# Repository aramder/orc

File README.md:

<div align="center">

<picture>
  <source media="(prefers-color-scheme: dark)" srcset="docs/media/banner-dark.svg">
  <source media="(prefers-color-scheme: light)" srcset="docs/media/banner-light.svg">
  
</picture>

**A replacement controller board for surplus Motorola PMUN1046A relay boxes — same relays and enclosure; open CAN control over plain terminal blocks instead of the proprietary wired link to the radio.**

Independent open-source project. Not affiliated with, endorsed by, or connected to Motorola Solutions, Inc. — see [TRADEMARKS.md](TRADEMARKS.md).

[**Project writeup and photos →**](https://aramd.net/PMUN1046A-Relay-Controller/)

**Safety:** this switches high-current DC in a vehicle. It is not safety qualified and must not be used for safety-critical functions. Read [DISCLAIMER.md](DISCLAIMER.md) before building anything.

</div>

---

## Why

The PMUN1046A **Universal Relay Controller (URC)** is a sealed 12 V automotive relay box — ten relay outputs at 15 A each, per-channel fusing, and a busbar power input rated for up to two cables at 60 A each (Motorola's install manual), in a trunnion-mounted weatherproof chassis. Power goes straight to the busbar through cable glands — no special harness needed on the input side. Surplus units are common and cheap. Everything about it is desirable *except* that it only takes commands from a Motorola APX radio over a proprietary GCAI/USB link.

ORC replaces the controller board outright and makes the box a general-purpose, openly-controlled ten-channel power distribution module. **ORC** stands for Open Relay Controller.

ORC does not implement, emulate, or interoperate with the GCAI link. The controller board is an independent design that replaces the donor unit's controller board entirely; control is plain CAN or USB.

<details>
<summary><b>About the donor unit</b> (PMUN1046A Universal Relay Controller)</summary>
<br>

Motorola's URC ships as part of the APX mobile radio ecosystem — a sealed relay box meant to switch scene lighting, sirens, and other accessory loads from the radio head. The relay board and chassis are generic 12 V automotive gear; only the controller board and its proprietary GCAI/USB command link to the radio are Motorola-specific. The relay board is entirely passive (relays, fuses, terminal blocks, busbar — no drivers or regulator of its own); a small internal harness carries switched 9 V coil drive between it and the controller board. Power input has no special harness at all — it lands straight on the busbar through the enclosure's cable glands. ORC keeps the relay board and chassis, and replaces the controller board and its proprietary radio link with plain CAN over terminal blocks — no proprietary connector anywhere in this design.

</details>

## What it is

<table>
<tr>
<td width="50%" valign="top">

**Inherited from the donor unit**
- Ten switched channels, 15 A each
- Per-channel fusing + busbar
- Board-to-board coil-drive harness (P/N `0975931M01`) — the internal cable between the relay board and the controller board, carrying switched 9 V coil drive; *not* a power-input harness
- Sealed, trunnion-mounted chassis

</td>
<td width="50%" valign="top">

**Rebuilt on the new controller board**
- ESP32-C3 controller (native USB for programming only; CAN-exclusive control, no wireless)
- 9 V relay coil supply
- Ten relay driver stages
- CAN terminal blocks (no proprietary connector)

</td>
</tr>
</table>

Category-wise this is a **PDM** (power distribution module) — the sPOD / Switch-Pros class of device — with an open CAN control interface instead of a proprietary wired link to the radio.

## The board

<em>ORC Rev A (green, right) and the OEM control PCB it replaces (blue, left).</em>

<em>ORC Rev A installed in the donor enclosure, alongside the OEM relay board that stays.</em>

**Full writeup, build story, and more photos:** [Open Relay Controller for the Motorola PMUN1046A](https://aramd.net/PMUN1046A-Relay-Controller/).

## Repo structure

One repo for design inputs, hardware, and firmware — no split-repo overhead for a project this size:

| Path | Contents | Status |
|---|---|---|
| `docs/` | Design inputs, specs, architecture decisions | Active |
| `hardware/` | KiCad project — schematic, PCB, BOM | Schematic captured, boards fabricated, populated, and bring-up verified on real hardware |
| `firmware/` | PlatformIO / Arduino firmware | `canopen_app` is real application firmware (CAN + USB relay control), verified on real hardware |
| `tools/` | Host-side CAN/USB bench test scripts | Used against real hardware |

## License

Different parts of the repo carry different licenses. Full texts are in [LICENSES/](LICENSES/); each directory also carries its own `LICENSE` file.

| Path | License |
|---|---|
| `hardware/` | [CERN-OHL-W-2.0](LICENSES/CERN-OHL-W-2.0.txt) |
| `firmware/`, `tools/` | [Apache-2.0](LICENSES/Apache-2.0.txt) |
| `docs/` | [CC-BY-4.0](LICENSES/CC-BY-4.0.txt) |

Hardware and software are licensed separately because they are separate works: under CERN-OHL's own definitions the ESP32-C3 is an Available Component, so a hardware license on the board does not reach the code running on it. See [NOTICE](NOTICE) for the summary and [TRADEMARKS.md](TRADEMARKS.md) for trademark and affiliation.

## Status

**Real-hardware bring-up complete.** Boards were sent to fab 2026-08-02, came back populated, and have been bench-tested since 2026-08-10: the PCA9555/I2C-isolator chain, the full 10-channel relay-driver mapping, and the CAN (RPDO1/TPDO1/TPDO2/Heartbeat) and USB control paths have all been exercised on real hardware. Five real firmware bugs were found and fixed along the way — BUG-001 through BUG-005, see [docs/features/LOG.md](docs/features/LOG.md) for the full history — the last of which (a liveness stall under an absent/unpowered PCA9555) was verified on real hardware 2026-09-04. One real mechanical fault (a harness connector shorting against the enclosure chassis) was also found and fixed on the bench — see [docs/circuit-draft.md](docs/circuit-draft.md) for the follow-up enclosure-clearance item.

No further active development is planned barring a new bug. A couple of feature requests (FR-003, FR-005) remain open in the backlog but aren't being actively pursued right now.

Working conventions for part selection, asset verification, and check gates: [docs/hardware-workflow.md](docs/hardware-workflow.md). Bench test tooling for talking to a real board over CAN/USB from a PC: [tools/](tools/).

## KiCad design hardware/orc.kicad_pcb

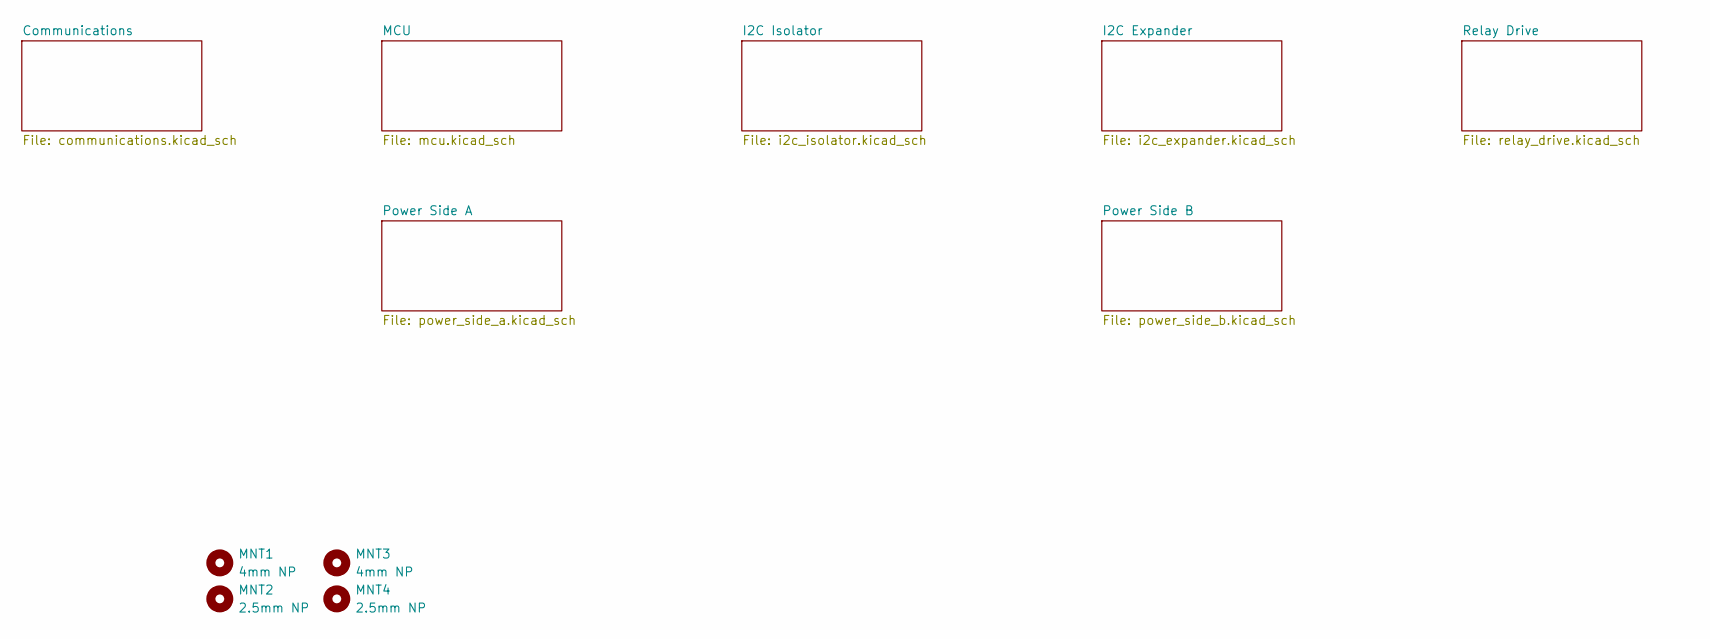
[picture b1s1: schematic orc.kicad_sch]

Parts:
MNT1, MNT3: 4mm NP; MountingHole_4mm
MNT2, MNT4: 2.5mm NP; MountingHole_2.5mm

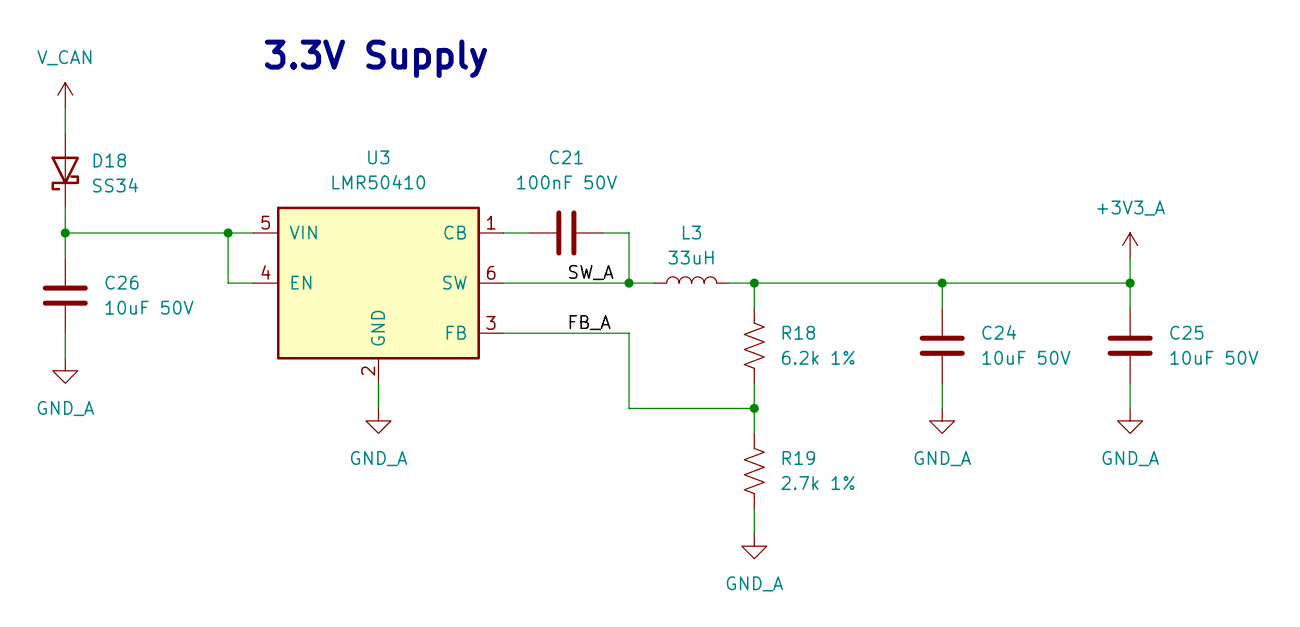
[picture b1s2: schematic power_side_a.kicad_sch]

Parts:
C21: 100nF 50V; C_0603_1608Metric; LCSC C14663
C24, C25, C26: 10uF 50V; C_0805_2012Metric; LCSC C440198
D18: SS34; D_SMA; LCSC C8678
L3: 33uH; L_Chilisin_BWVS00606045; Manufacturer Part Number SMDRI127-680MT; LCSC C285825
R18: 6.2k 1%; R_0603_1608Metric; LCSC C4260
R19: 2.7k 1%; R_0603_1608Metric; LCSC C13167
U3: LMR50410; SOT-23-6

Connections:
+3V3_A: C24.2, C25.2, L3.2, R18.2; also elsewhere on the board
/Power Side A/FB_A: R18.1, R19.2, U3.3 (FB)
/Power Side A/SW_A: C21.1, L3.1, U3.6 (SW)
GND_A: C24.1, C25.1, C26.1, R19.1, U3.2 (GND); also elsewhere on the board
unnamed: C26.2, D18.1 (K), U3.4 (EN), U3.5 (VIN)
unnamed: C21.2, U3.1 (CB)
V_CAN: D18.2 (A); also elsewhere on the board

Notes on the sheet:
3.3V Supply

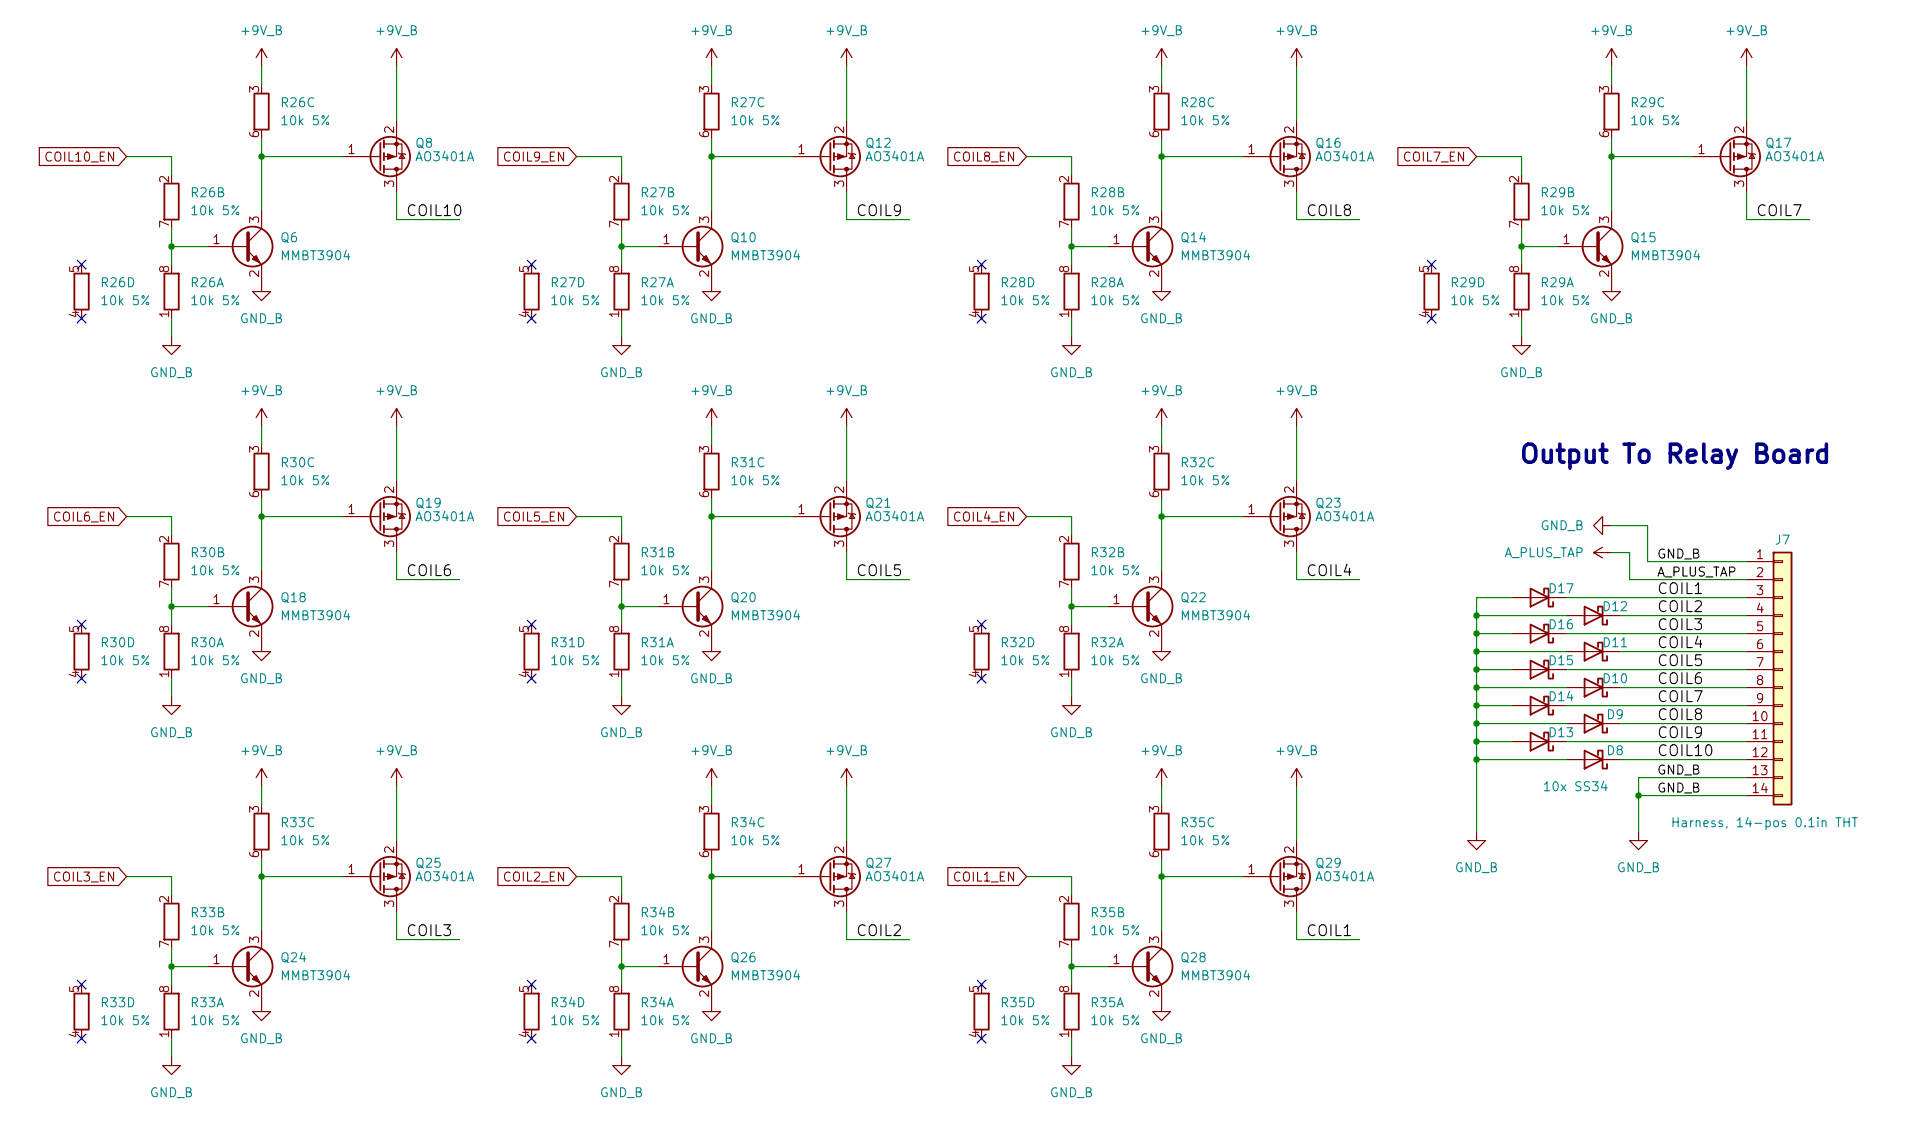
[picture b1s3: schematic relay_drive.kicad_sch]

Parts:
D8, D9, D10, D11, D12, D13, D14, D15, D16: SS34; D_SMA; LCSC C8678
D17: 10x SS34; D_SMA; LCSC C8678
J7: Harness, 14-pos 0.1in THT; PinSocket_1x14_P2.54mm_Vertical
Q6: MMBT3904; SOT-23; LCSC C20526
Q8, Q12, Q16, Q17, Q19, Q21, Q23, Q25, Q27, Q29: AO3401A; SOT-23; LCSC C15127
Q10, Q14, Q15, Q18, Q20, Q22, Q24, Q26, Q28: MMBT3904; SOT-23
R26, R27, R28, R29, R30, R31, R32, R33, R34, R35: 10k 5%; R_Array_Concave_4x0603; LCSC C29718

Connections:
+9V_B: Q8.2 (S), Q12.2 (S), Q16.2 (S), Q17.2 (S), Q19.2 (S), Q21.2 (S), Q23.2 (S), Q25.2 (S), Q27.2 (S), Q29.2 (S), R26.3 (R3.1), R27.3 (R3.1), R28.3 (R3.1), R29.3 (R3.1), R30.3 (R3.1), R31.3 (R3.1), R32.3 (R3.1), R33.3 (R3.1), R34.3 (R3.1), R35.3 (R3.1); also elsewhere on the board
/Relay Drive/COIL1: D17.1 (K), J7.3, Q29.3 (D)
/Relay Drive/COIL2: D12.1 (K), J7.4, Q27.3 (D)
/Relay Drive/COIL3: D16.1 (K), J7.5, Q25.3 (D)
/Relay Drive/COIL4: D11.1 (K), J7.6, Q23.3 (D)
/Relay Drive/COIL5: D15.1 (K), J7.7, Q21.3 (D)
/Relay Drive/COIL6: D10.1 (K), J7.8, Q19.3 (D)
/Relay Drive/COIL7: D14.1 (K), J7.9, Q17.3 (D)
/Relay Drive/COIL8: D9.1 (K), J7.10, Q16.3 (D)
/Relay Drive/COIL9: D13.1 (K), J7.11, Q12.3 (D)
/Relay Drive/COIL10: D8.1 (K), J7.12, Q8.3 (D)
A_PLUS_TAP: J7.2; also elsewhere on the board
COIL1_EN: R35.2 (R2.1); also elsewhere on the board
COIL2_EN: R34.2 (R2.1); also elsewhere on the board
COIL3_EN: R33.2 (R2.1); also elsewhere on the board
COIL4_EN: R32.2 (R2.1); also elsewhere on the board
COIL5_EN: R31.2 (R2.1); also elsewhere on the board
COIL6_EN: R30.2 (R2.1); also elsewhere on the board
COIL7_EN: R29.2 (R2.1); also elsewhere on the board
COIL8_EN: R28.2 (R2.1); also elsewhere on the board
COIL9_EN: R27.2 (R2.1); also elsewhere on the board
COIL10_EN: R26.2 (R2.1); also elsewhere on the board
GND_B: D8.2 (A), D9.2 (A), D10.2 (A), D11.2 (A), D12.2 (A), D13.2 (A), D14.2 (A), D15.2 (A), D16.2 (A), D17.2 (A), J7.1, J7.13, J7.14, Q6.2 (E), Q10.2 (E), Q14.2 (E), Q15.2 (E), Q18.2 (E), Q20.2 (E), Q22.2 (E), Q24.2 (E), Q26.2 (E), Q28.2 (E), R26.1 (R1.1), R27.1 (R1.1), R28.1 (R1.1), R29.1 (R1.1), R30.1 (R1.1), R31.1 (R1.1), R32.1 (R1.1), R33.1 (R1.1), R34.1 (R1.1), R35.1 (R1.1); also elsewhere on the board
unnamed: Q6.1 (B), R26.7 (R2.2), R26.8 (R1.2)
unnamed: Q6.3 (C), Q8.1 (G), R26.6 (R3.2)
unnamed: Q10.1 (B), R27.7 (R2.2), R27.8 (R1.2)
unnamed: Q10.3 (C), Q12.1 (G), R27.6 (R3.2)
unnamed: Q14.1 (B), R28.7 (R2.2), R28.8 (R1.2)
unnamed: Q14.3 (C), Q16.1 (G), R28.6 (R3.2)
unnamed: Q15.1 (B), R29.7 (R2.2), R29.8 (R1.2)
unnamed: Q15.3 (C), Q17.1 (G), R29.6 (R3.2)
unnamed: Q18.1 (B), R30.7 (R2.2), R30.8 (R1.2)
unnamed: Q18.3 (C), Q19.1 (G), R30.6 (R3.2)
unnamed: Q20.1 (B), R31.7 (R2.2), R31.8 (R1.2)
unnamed: Q20.3 (C), Q21.1 (G), R31.6 (R3.2)
unnamed: Q22.1 (B), R32.7 (R2.2), R32.8 (R1.2)
unnamed: Q22.3 (C), Q23.1 (G), R32.6 (R3.2)
unnamed: Q24.1 (B), R33.7 (R2.2), R33.8 (R1.2)
unnamed: Q24.3 (C), Q25.1 (G), R33.6 (R3.2)
unnamed: Q26.1 (B), R34.7 (R2.2), R34.8 (R1.2)
unnamed: Q26.3 (C), Q27.1 (G), R34.6 (R3.2)
unnamed: Q28.1 (B), R35.7 (R2.2), R35.8 (R1.2)
unnamed: Q28.3 (C), Q29.1 (G), R35.6 (R3.2)

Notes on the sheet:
Output To Relay Board

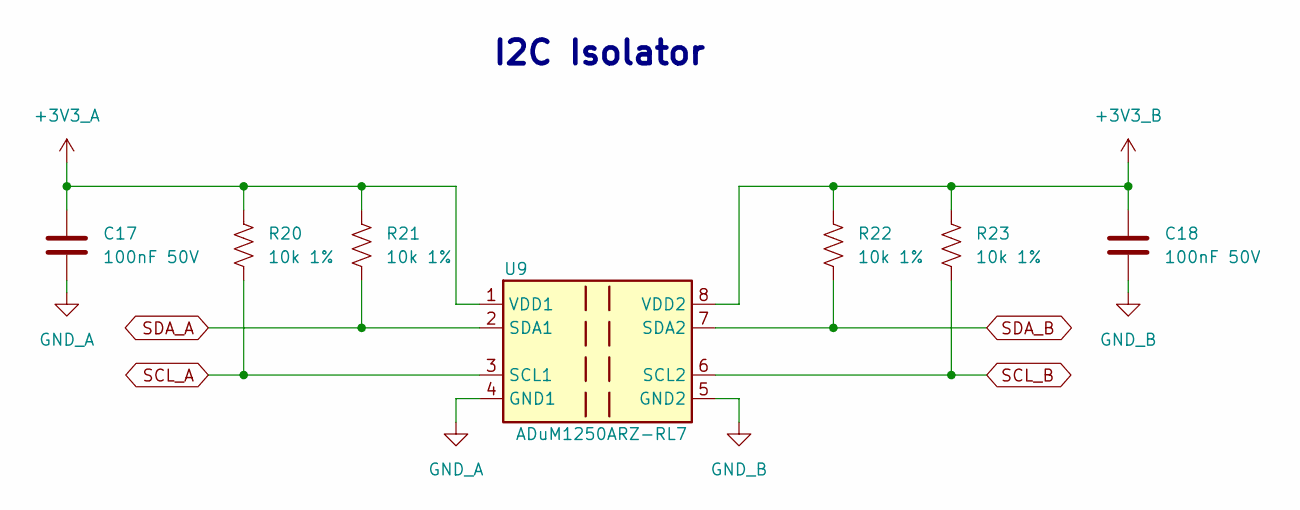
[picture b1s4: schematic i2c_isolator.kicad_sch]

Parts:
C17, C18: 100nF 50V; C_0603_1608Metric; LCSC C14663
R20, R21, R22, R23: 10k 1%; R_0603_1608Metric; LCSC C25804
U9: ADuM1250ARZ-RL7; SOIC-8_3.9x4.9mm_P1.27mm; LCSC C13839

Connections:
+3V3_A: C17.2, R20.1, R21.1, U9.1 (VDD1); also elsewhere on the board
+3V3_B: C18.2, R22.1, R23.1, U9.8 (VDD2); also elsewhere on the board
GND_A: C17.1, U9.4 (GND1); also elsewhere on the board
GND_B: C18.1, U9.5 (GND2); also elsewhere on the board
SCL_A: R20.2, U9.3 (SCL1); also elsewhere on the board
SCL_B: R23.2, U9.6 (SCL2); also elsewhere on the board
SDA_A: R21.2, U9.2 (SDA1); also elsewhere on the board
SDA_B: R22.2, U9.7 (SDA2); also elsewhere on the board

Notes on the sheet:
I2C Isolator

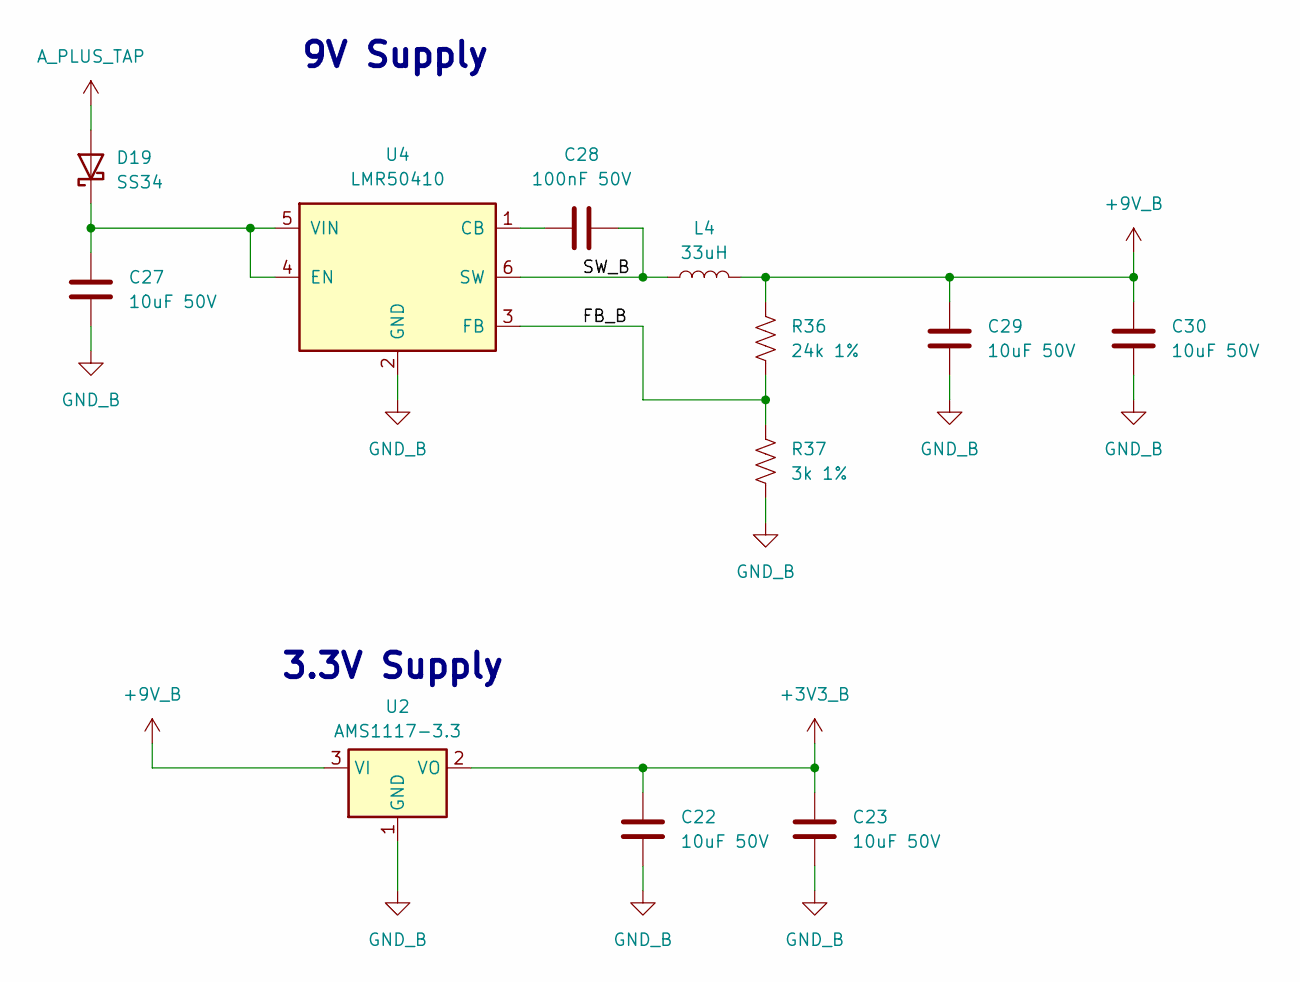
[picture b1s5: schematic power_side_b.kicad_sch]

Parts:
C22, C23, C27, C29, C30: 10uF 50V; C_0805_2012Metric; LCSC C440198
C28: 100nF 50V; C_0603_1608Metric; LCSC C14663
D19: SS34; D_SMA; LCSC C8678
L4: 33uH; L_Chilisin_BWVS00606045; Manufacturer Part Number SMDRI127-680MT; LCSC C285825
R36: 24k 1%; R_0603_1608Metric; LCSC C23352
R37: 3k 1%; R_0603_1608Metric; LCSC C4211
U2: AMS1117-3.3; SOT-223-3_TabPin2; LCSC C6186
U4: LMR50410; SOT-23-6

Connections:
+3V3_B: C22.2, C23.2, U2.2 (VO); also elsewhere on the board
+9V_B: C29.2, C30.2, L4.2, R36.2, U2.3 (VI); also elsewhere on the board
/Power Side B/FB_B: R36.1, R37.2, U4.3 (FB)
/Power Side B/SW_B: C28.1, L4.1, U4.6 (SW)
A_PLUS_TAP: D19.2 (A); also elsewhere on the board
GND_B: C22.1, C23.1, C27.1, C29.1, C30.1, R37.1, U2.1 (GND), U4.2 (GND); also elsewhere on the board
unnamed: C27.2, D19.1 (K), U4.4 (EN), U4.5 (VIN)
unnamed: C28.2, U4.1 (CB)

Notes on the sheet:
9V Supply
3.3V Supply

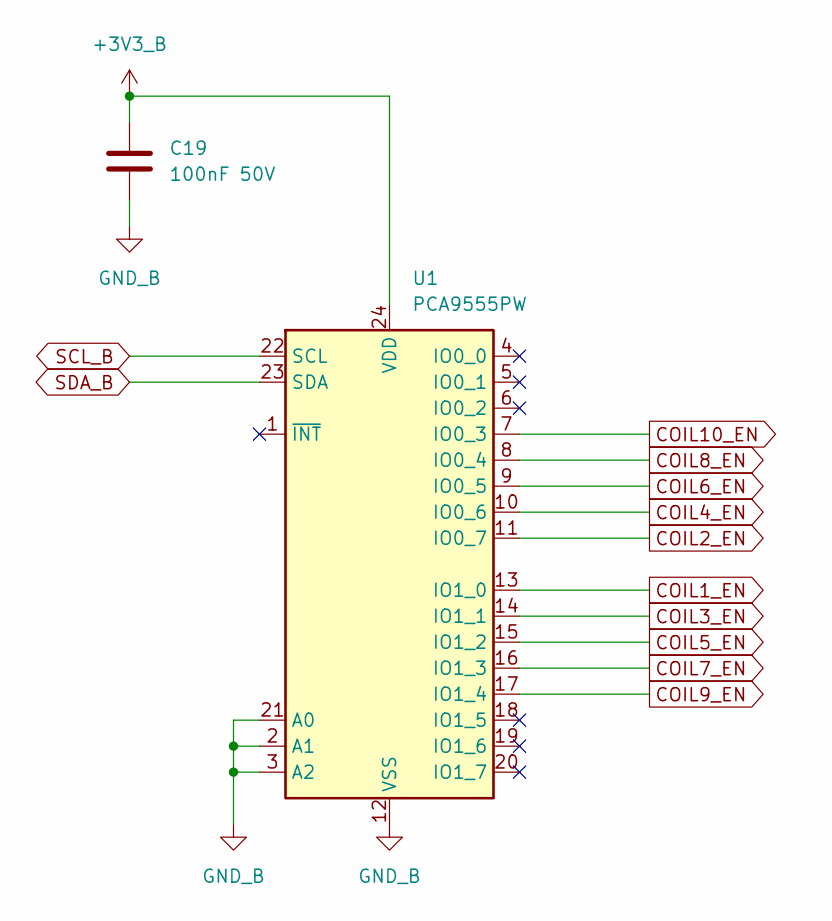
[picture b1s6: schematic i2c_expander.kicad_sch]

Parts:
C19: 100nF 50V; C_0603_1608Metric; LCSC C14663
U1: PCA9555PW; TSSOP-24_4.4x7.8mm_P0.65mm; LCSC C128392

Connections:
+3V3_B: C19.2, U1.24 (VDD); also elsewhere on the board
COIL1_EN: U1.13 (IO1_0); also elsewhere on the board
COIL2_EN: U1.11 (IO0_7); also elsewhere on the board
COIL3_EN: U1.14 (IO1_1); also elsewhere on the board
COIL4_EN: U1.10 (IO0_6); also elsewhere on the board
COIL5_EN: U1.15 (IO1_2); also elsewhere on the board
COIL6_EN: U1.9 (IO0_5); also elsewhere on the board
COIL7_EN: U1.16 (IO1_3); also elsewhere on the board
COIL8_EN: U1.8 (IO0_4); also elsewhere on the board
COIL9_EN: U1.17 (IO1_4); also elsewhere on the board
COIL10_EN: U1.7 (IO0_3); also elsewhere on the board
GND_B: C19.1, U1.2 (A1), U1.3 (A2), U1.12 (VSS), U1.21 (A0); also elsewhere on the board
SCL_B: U1.22 (SCL); also elsewhere on the board
SDA_B: U1.23 (SDA); also elsewhere on the board

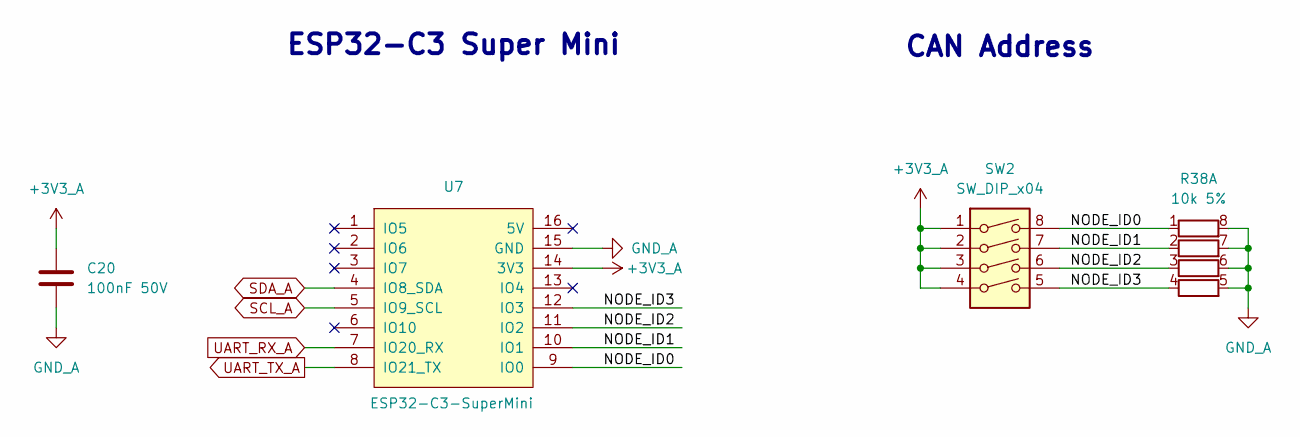
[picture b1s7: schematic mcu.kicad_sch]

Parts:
C20: 100nF 50V; C_0603_1608Metric; LCSC C14663
R38: 10k 5%; R_Array_Concave_4x0603; LCSC C29718
SW2: SW_DIP_x04; SOIC-8_5.3x5.3mm_P1.27mm; LCSC C3293144
U7: ESP32-C3-SuperMini

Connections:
+3V3_A: C20.2, SW2.1, SW2.2, SW2.3, SW2.4, U7.14 (3V3); also elsewhere on the board
/MCU/NODE_ID0: R38.1 (R1.1), SW2.8, U7.9 (IO0)
/MCU/NODE_ID1: R38.2 (R2.1), SW2.7, U7.10 (IO1)
/MCU/NODE_ID2: R38.3 (R3.1), SW2.6, U7.11 (IO2)
/MCU/NODE_ID3: R38.4 (R4.1), SW2.5, U7.12 (IO3)
GND_A: C20.1, R38.5 (R4.2), R38.6 (R3.2), R38.7 (R2.2), R38.8 (R1.2), U7.15 (GND); also elsewhere on the board
SCL_A: U7.5 (IO9_SCL); also elsewhere on the board
SDA_A: U7.4 (IO8_SDA); also elsewhere on the board
UART_RX_A: U7.7 (IO20_RX); also elsewhere on the board
UART_TX_A: U7.8 (IO21_TX); also elsewhere on the board

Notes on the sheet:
ESP32-C3 Super Mini
CAN Address

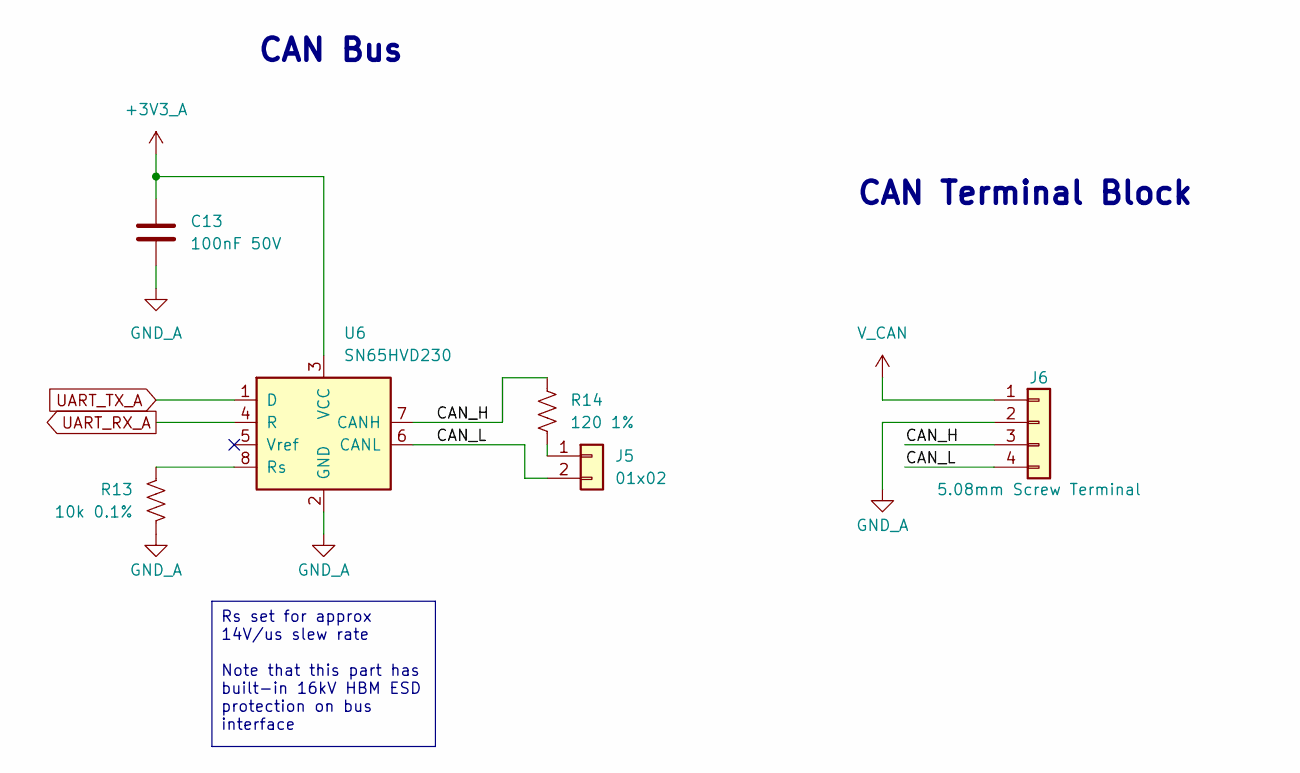
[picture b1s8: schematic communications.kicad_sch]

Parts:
C13: 100nF 50V; C_0603_1608Metric; LCSC C14663
J5: 01x02; PinHeader_1x02_P2.54mm_Vertical; LCSC C492401
J6: 5.08mm Screw Terminal; Samtec_HPM-04-01-x-S_Straight_1x04_Pitch5.08mm; LCSC C2827883
R13: 10k 0.1%; R_0603_1608Metric; LCSC C95204
R14: 120 1%; R_1206_3216Metric; LCSC C17909
U6: SN65HVD230; SOIC-8_3.9x4.9mm_P1.27mm; LCSC C12084

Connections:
+3V3_A: C13.2, U6.3 (VCC); also elsewhere on the board
/Communications/CAN_H: J6.3, R14.2, U6.7 (CANH)
/Communications/CAN_L: J5.2, J6.4, U6.6 (CANL)
GND_A: C13.1, J6.2, R13.1, U6.2 (GND); also elsewhere on the board
unnamed: J5.1, R14.1
unnamed: R13.2, U6.8 (Rs)
UART_RX_A: U6.4 (R); also elsewhere on the board
UART_TX_A: U6.1 (D); also elsewhere on the board
V_CAN: J6.1; also elsewhere on the board

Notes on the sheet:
CAN Bus
CAN Terminal Block
Rs set for approx 14V/us slew rate Note that this part has built-in 16kV HBM ESD protection on bus interface

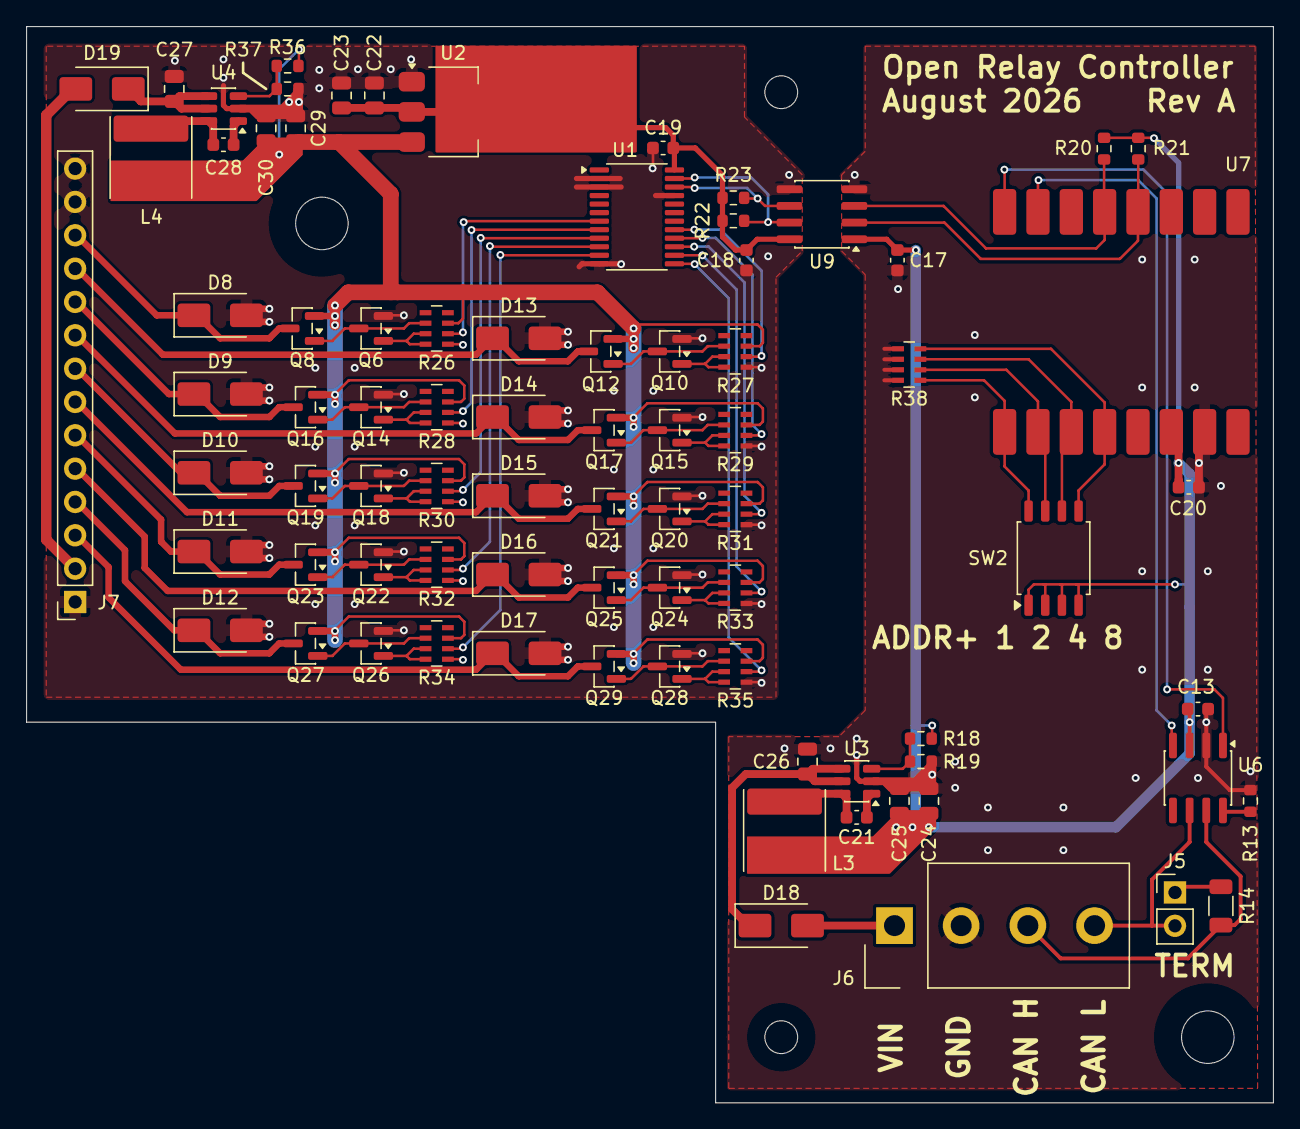
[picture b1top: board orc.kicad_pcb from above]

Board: 2 copper layers, 95.0 x 82.0 mm, 85 parts (0 on the bottom side), 69 nets.
